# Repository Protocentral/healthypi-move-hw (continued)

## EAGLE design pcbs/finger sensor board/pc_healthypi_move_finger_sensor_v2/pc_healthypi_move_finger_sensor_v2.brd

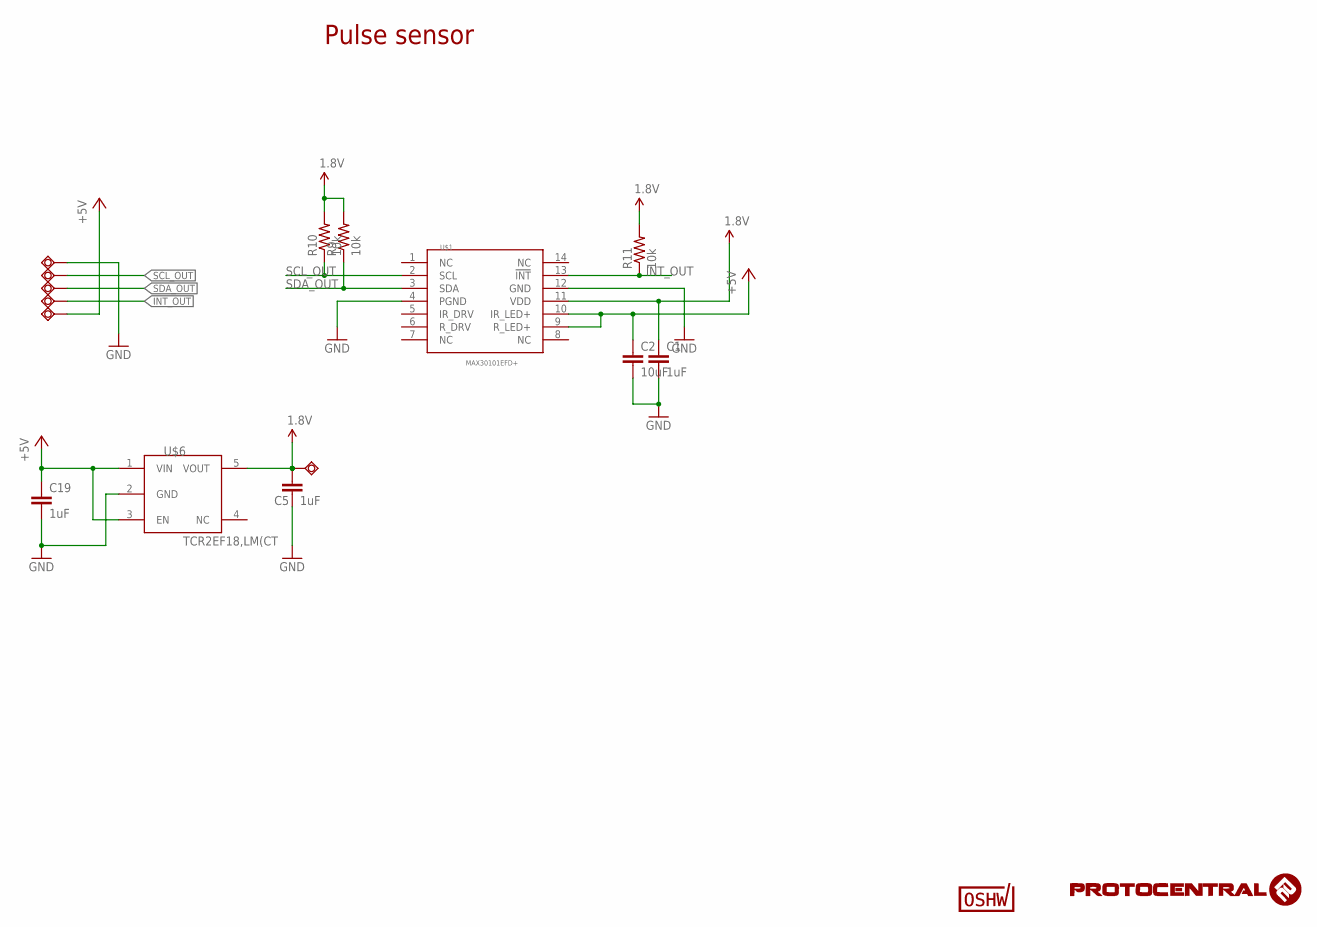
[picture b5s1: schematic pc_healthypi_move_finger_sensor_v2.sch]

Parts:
C1, C5, C19: 1uF; C0402
C2: 10uF; C0402
R9, R10, R11: 10k; R0402
SWIO1, SWIO2, SWIO3, SWIO4, SWIO5, SWIO6: TPSQTP11R; TP11R
U$1: MAX30101EFD+; OESIP-14
U$6: TCR2EF18,LM(CT; SOT95P285X140-5N
U$9: CERT-SMALL; CERT-SMALL-SILK

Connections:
1.8V: C1.1, C5.1, R9.2, R10.2, R11.2, SWIO5.TP, U$1.11 (VDD), U$6.5 (VOUT)
+5V: C2.1, C19.1, SWIO4.TP, U$1.9 (R_LED+), U$1.10 (IR_LED+), U$6.1 (VIN), U$6.3 (EN)
GND: C1.2, C2.2, C5.2, C19.2, SWIO6.TP, U$1.4 (PGND), U$1.12 (GND), U$6.2 (GND)
INT_OUT: R11.1, SWIO3.TP, U$1.13 (!INT)
SCL_OUT: R10.1, SWIO1.TP, U$1.2 (SCL)
SDA_OUT: R9.1, SWIO2.TP, U$1.3 (SDA)

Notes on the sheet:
Pulse sensor

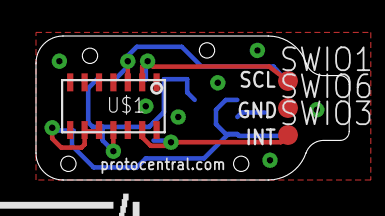
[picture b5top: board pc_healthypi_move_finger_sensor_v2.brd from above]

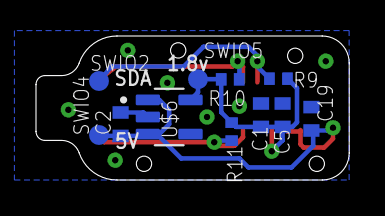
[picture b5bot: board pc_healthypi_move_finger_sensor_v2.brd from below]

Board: 2 copper layers, 17.4 x 8.0 mm, 16 parts (11 on the bottom side), 6 nets.

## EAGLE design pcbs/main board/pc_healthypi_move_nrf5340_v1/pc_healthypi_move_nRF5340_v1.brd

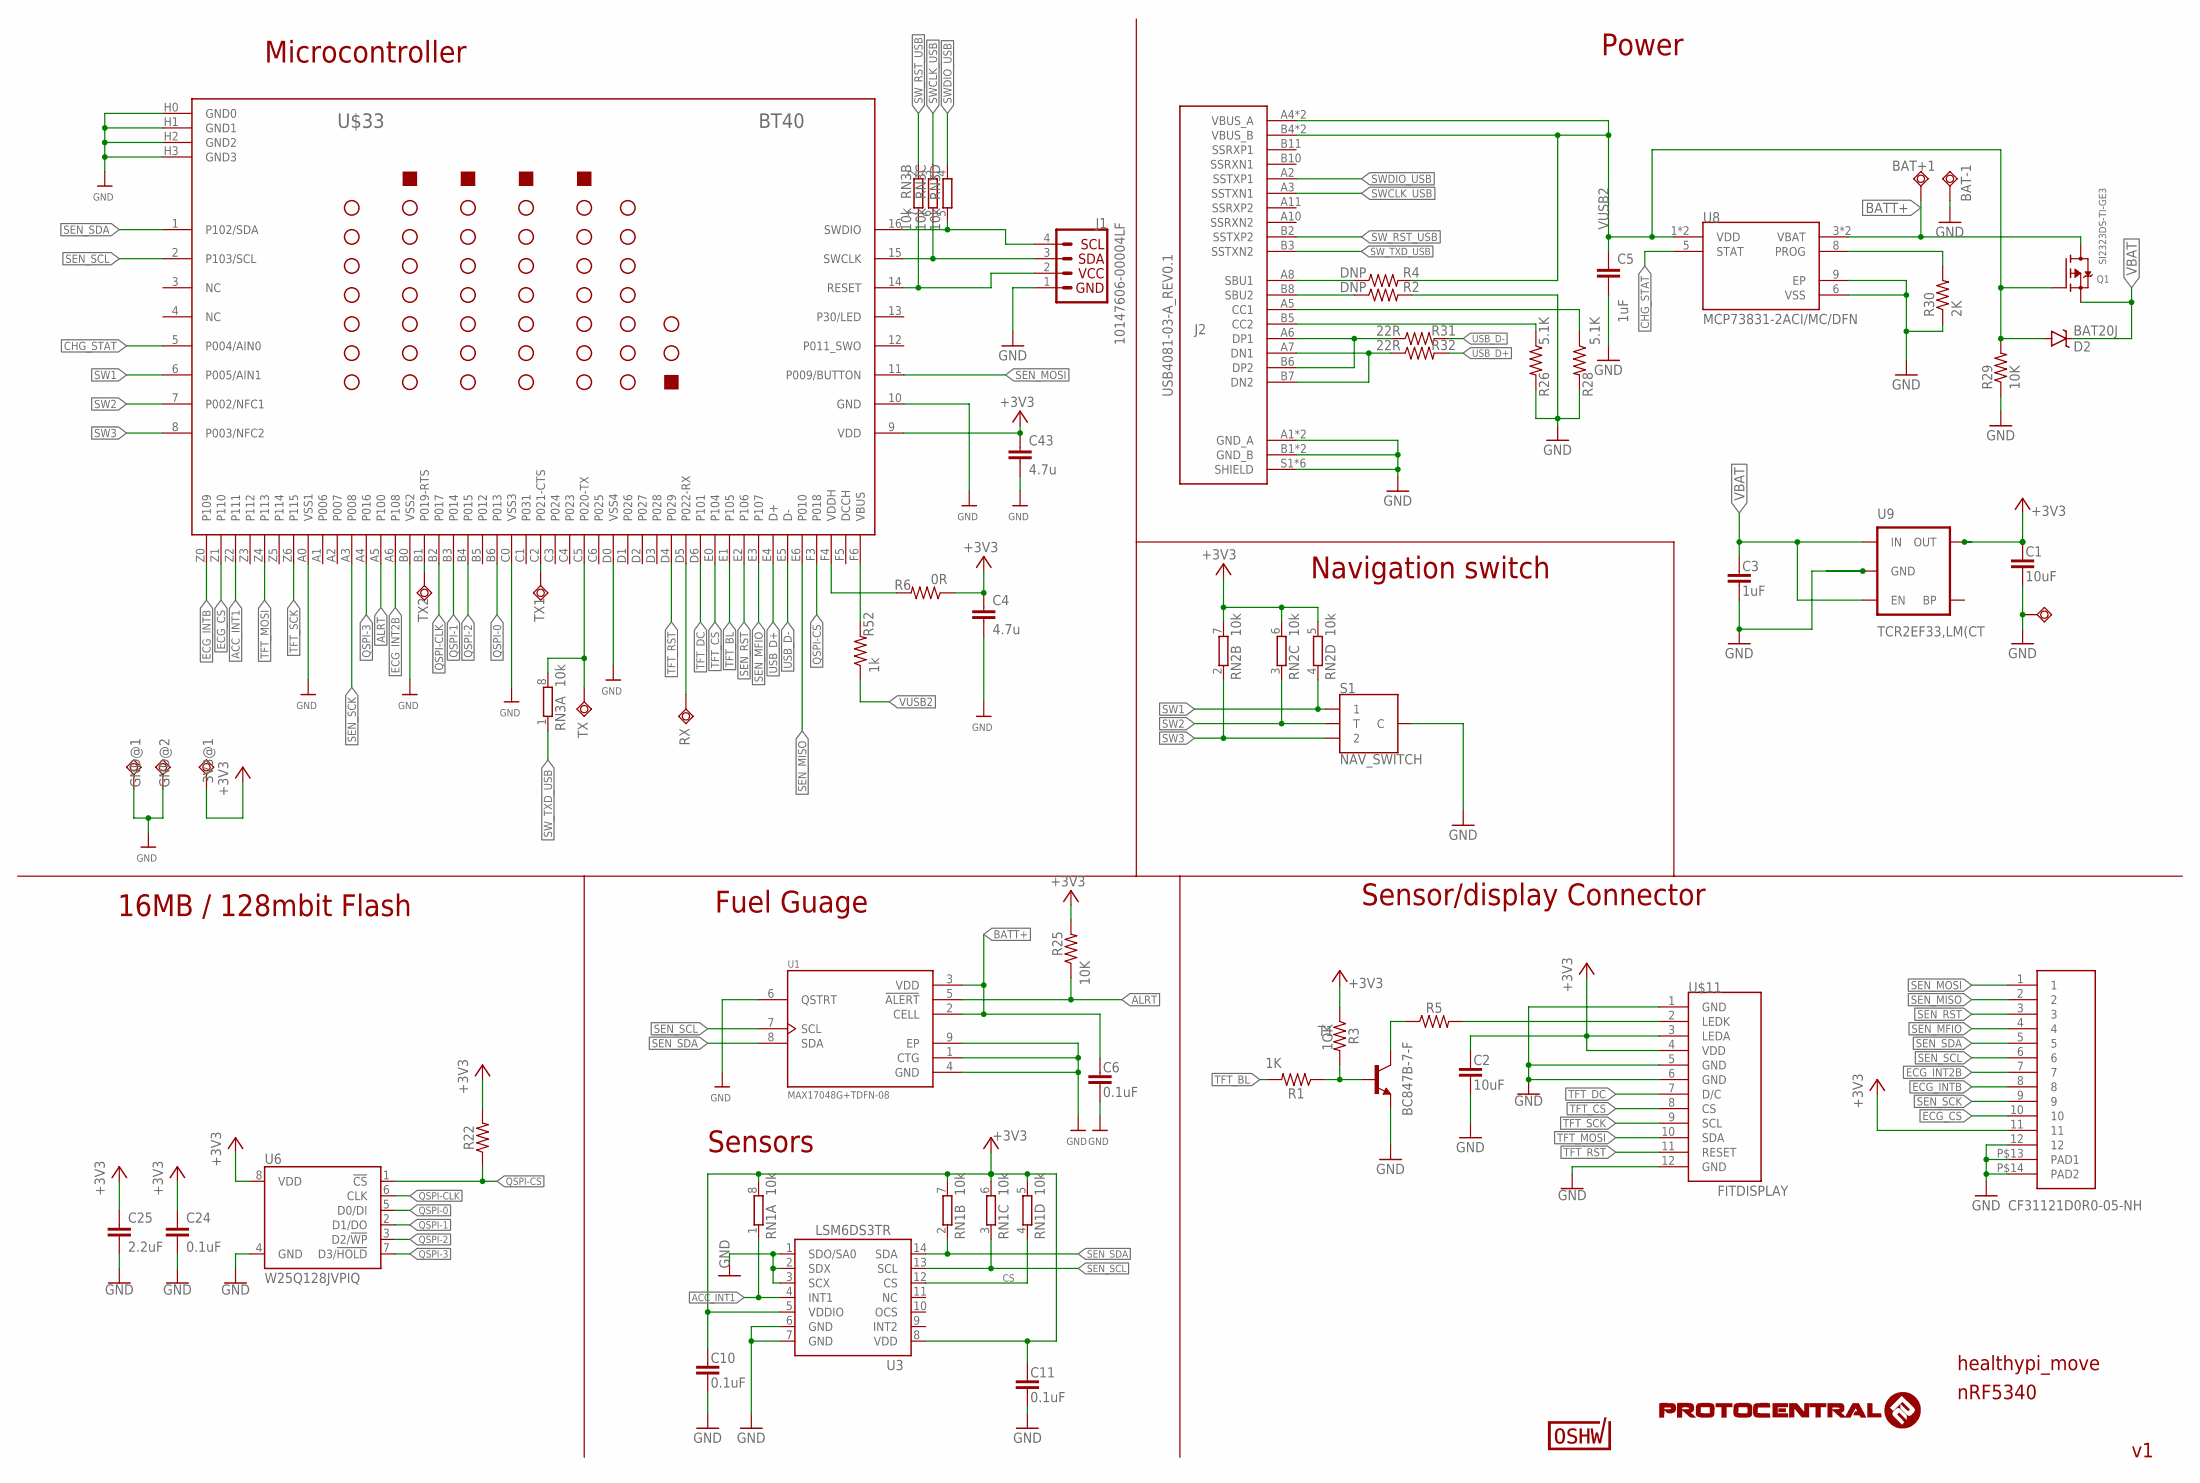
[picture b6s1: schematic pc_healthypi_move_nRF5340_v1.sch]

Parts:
3V3@1: TPSQTP13SQ; TP13SQ
BAT+1: TPSQTP13SQ; TP13SQ
BAT-1: TPSQTP13SQ; TP13SQ
C1, C2: 10uF; 0603@1
C3, C5: 1uF; 0402-TIGHT
C4, C43: 4.7u; C0402
C6, C10, C11, C24: 0.1uF; 0402-TIGHT
C25: 2.2uF; 0402-TIGHT
D2: BAT20J; SOD-323
GND@1, GND@2: TPSQTP13SQ; TP13SQ
J1: 10147606-00004LF; JST04_1MM_RA
J2: USB4081-03-A_REV0.1; GCT_USB4081-03-A_REV0.1
Q1: SI2323DS-TI-GE3; SOT23-R
R1, R3: 200; R0402
R2, R4: DNP; 0402-RES
R5: 200R; R0402
R6: 0R; 0402-RES
R22: 10k; R0402
R25: 10K; 0402-RES
R26, R28: 5.1K; 0402-RES
R29: 10K; R0402
R30: 2K; R0402
R31, R32: 22R; 0402-RES
R52: 1k; 0402-RES
RN1, RN2, RN3: 10k; 4X0402ARV341
RX: TPSQTP13SQ; TP13SQ
S1: NAV_SWITCH
SWIO6: TPSQTP11R; TP11R
T1: BC847B-7-F; SOT23-BEC
TX, TX1, TX2: TPSQTP13SQ; TP13SQ
U1: MAX17048G+TDFN-08; SON50P200X200X80-9N
U3: LSM6DS3TR; LGA14L
U6: W25Q128JVPIQ; WSON-8-6X5-SKINNY_CENTERPAD
U8: MCP73831-2ACI/MC/DFN; SON50P200X300X100-9N
U9: TCR2EF33,LM(CT; SOT23-5
U$5: CF31121D0R0-05-NH
U$9: CERT-SMALL; CERT-SMALL-SILK
U$11: FITDISPLAY
U$33: BT40

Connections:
+3V3: 3V3@1.TP, C1.1, C2.1, C4.1, C10.1, C11.1, C24.1, C25.1, C43.1, R3.1, R6.1, R22.2, R25.2, RN1.5 (2), RN1.6 (2), RN1.7 (2), RN1.8 (2), RN2.5 (2), RN2.6 (2), RN2.7 (2), U3.5 (VDDIO), U3.8 (VDD), U6.8 (VDD), U9.5 (OUT), U$5.11, U$11.3 (LEDA), U$11.4 (VDD), U$33.9 (VDD)
ACC_INT1: RN1.1, U3.4 (INT1), U$33.Z2 (P111)
ALRT: R25.1, U1.5 (!ALERT), U$33.A5 (P100)
BATT+: BAT+1.TP, C6.1, Q1.3 (D), U1.2 (CELL), U1.3 (VDD), U8.3 (VBAT), U8.4 (VBAT)
CHG_STAT: U8.5 (STAT), U$33.5 (P004/AIN0)
CS: RN1.4 (1), U3.12 (CS)
ECG_CS: U$5.10, U$33.Z1 (P110)
ECG_INT2B: U$5.7, U$33.A6 (P108)
ECG_INTB: U$5.8, U$33.Z0 (P109)
GND: BAT-1.TP, C1.2, C2.2, C3.2, C4.2, C5.2, C6.2, C10.2, C11.2, C24.2, C25.2, C43.2, GND@1.TP, GND@2.TP, J1.1, J2.A1 (GND_A), J2.A12 (GND_A), J2.B1 (GND_B), J2.B12 (GND_B), J2.S1 (SHIELD), J2.S2 (SHIELD), J2.S3 (SHIELD), J2.S4 (SHIELD), J2.S5 (SHIELD), J2.S6 (SHIELD), R2.2, R26.2, R28.2, R29.1, R30.1, S1.C, SWIO6.TP, T1.E, U1.1 (CTG), U1.4 (GND), U1.6 (QSTRT), U1.9 (EP), U3.1 (SDO/SA0), U3.2 (SDX), U3.3 (SCX), U3.6 (GND), U3.7 (GND), U6.4 (GND), U8.6 (VSS), U8.9 (EP), U9.2 (GND), U$5.12, U$5.P$13 (PAD1), U$5.P$14 (PAD2), U$11.1 (GND), U$11.5 (GND), U$11.6 (GND), U$11.12 (GND), U$33.10 (GND), U$33.A0 (VSS1), U$33.B0 (VSS2), U$33.C0 (VSS3), U$33.D0 (VSS4), U$33.H0 (GND0), U$33.H1 (GND1), U$33.H2 (GND2), U$33.H3 (GND3)
unnamed: J2.B8 (SBU2), R2.1
unnamed: J2.A8 (SBU1), R4.1
unnamed: TX2.TP, U$33.B1 (P019-RTS)
unnamed: J2.B5 (CC2), R26.1
unnamed: TX1.TP, U$33.C2 (P021-CTS)
unnamed: J2.A5 (CC1), R28.1
unnamed: R30.2, U8.8 (PROG)
unnamed: J2.A6 (DP1), J2.B6 (DP2), R31.1
unnamed: J2.A7 (DN1), J2.B7 (DN2), R32.1
unnamed: R5.2, U$11.2 (LEDK)
unnamed: R5.1, T1.C
unnamed: R1.1, R3.2, T1.B
unnamed: R52.2, U$33.F6 (VBUS)
unnamed: R6.2, U$33.F4 (VDDH)
QSPI-0: U6.5 (D0/DI), U$33.B6 (P013)
QSPI-1: U6.2 (D1/DO), U$33.B3 (P014)
QSPI-2: U6.3 (D2/!WP!), U$33.B4 (P015)
QSPI-3: U6.7 (D3/!HOLD!), U$33.A4 (P016)
QSPI-CLK: U6.6 (CLK), U$33.B2 (P017)
QSPI-CS: R22.1, U6.1 (!CS!), U$33.F3 (P018)
RESET1: J1.2, RN3.7 (2), U$33.14 (RESET)
SEN_MFIO: U$5.4, U$33.E3 (P107)
SEN_MISO: U$5.2, U$33.E6 (P010)
SEN_MOSI: U$5.1, U$33.11 (P009/BUTTON)
SEN_RST: U$5.3, U$33.E2 (P106)
SEN_SCK: U$5.9, U$33.A3 (P008)
SEN_SCL: RN1.3 (1), U1.7 (SCL), U3.13 (SCL), U$5.6, U$33.2 (P103/SCL)
SEN_SDA: RN1.2 (1), U1.8 (SDA), U3.14 (SDA), U$5.5, U$33.1 (P102/SDA)
SW1: RN2.4 (1), S1.1, U$33.6 (P005/AIN1)
SW2: RN2.3 (1), S1.T, U$33.7 (P002/NFC1)
SW3: RN2.2 (1), S1.2, U$33.8 (P003/NFC2)
SWCLK1: J1.3, RN3.6 (2), U$33.15 (SWCLK)
SWCLK_USB: J2.A3 (SSTXN1), RN3.3 (1)
SWDIO1: J1.4, RN3.5 (2), U$33.16 (SWDIO)
SWDIO_USB: J2.A2 (SSTXP1), RN3.4 (1)
SW_RST_USB: J2.B2 (SSTXP2), RN3.2 (1)
SW_TXD_USB: J2.B3 (SSTXN2), RN3.1
TFT_BL: R1.2, U$33.E1 (P105)
TFT_CS: U$11.8 (CS), U$33.E0 (P104)
TFT_DC: U$11.7 (D/C), U$33.D6 (P101)
TFT_MOSI: U$11.10 (SDA), U$33.Z4 (P113)
TFT_RST: U$11.11 (RESET), U$33.D4 (P029)
TFT_SCK: U$11.9 (SCL), U$33.Z6 (P115)
UART_RX: RX.TP, U$33.D5 (P022-RX)
UART_TX: RN3.8 (2), TX.TP, U$33.C5 (P020-TX)
USB_D+: R32.2, U$33.E4 (D+)
USB_D-: R31.2, U$33.E5 (D-)
VBAT: C3.1, D2.C, Q1.2 (S), U9.1 (IN), U9.3 (EN)
VUSB2: C5.1, D2.A, J2.A4 (VBUS_A), J2.A9 (VBUS_A), J2.B4 (VBUS_B), J2.B9 (VBUS_B), Q1.1 (G), R4.2, R29.2, R52.1, U8.1 (VDD), U8.2 (VDD)

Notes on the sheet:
Power
nRF5340
Fuel Guage
Sensors
Sensor/display Connector
16MB / 128mbit Flash
1OK
CF31121D0R0-05-NH
Microcontroller
healthypi_move
Navigation switch

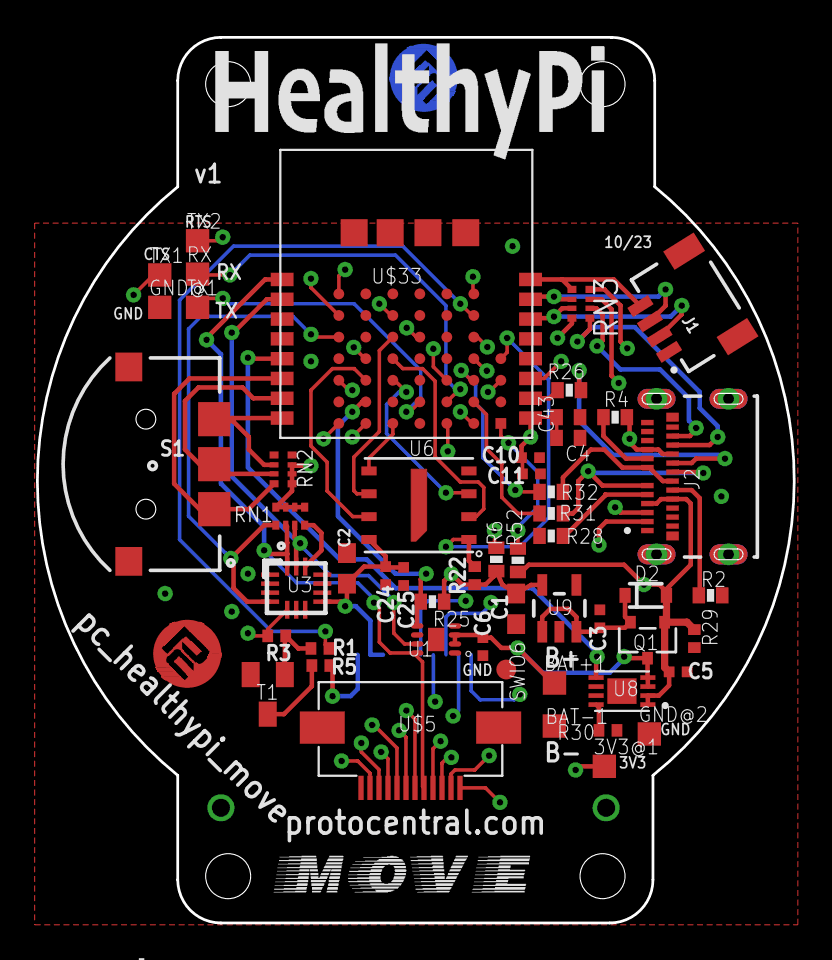
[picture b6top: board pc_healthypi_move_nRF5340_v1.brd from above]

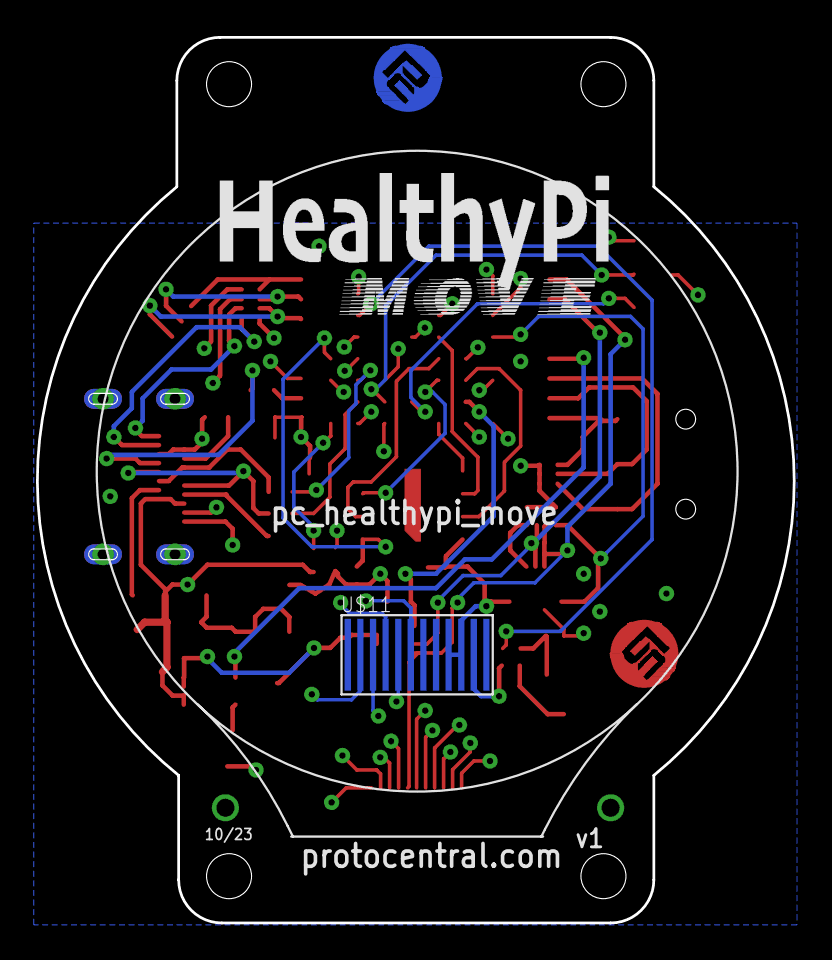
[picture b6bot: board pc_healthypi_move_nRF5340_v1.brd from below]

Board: 4 copper layers, 42.0 x 49.2 mm, 60 parts (4 on the bottom side), 59 nets.

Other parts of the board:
U$1, U$13: HEALTHYPI_MOVE_LOGO
U$6, U$10: HEALTHYPI_MOVE_LOGO_1
U$14, U$15: PCROUNDLOGO_GOLD
